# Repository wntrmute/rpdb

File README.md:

# Robot Power Distribution Board

This is a simple power distribution board that offers direct output to a motor controller, stable 5V and 3.3V rails, and an I2C expander.

## Version history

* [4.0](v4/) - added power and motor LEDs with SMD resistors
* [3.0](v3/) - updated silkscreen to improve capacitor placement
* [2.0](v2/) - first working prototype.

## Specifications

* Input voltage: 6-12V
* Max current: 1.2A draw through the 5V and 800 mA through the 3.3V rails

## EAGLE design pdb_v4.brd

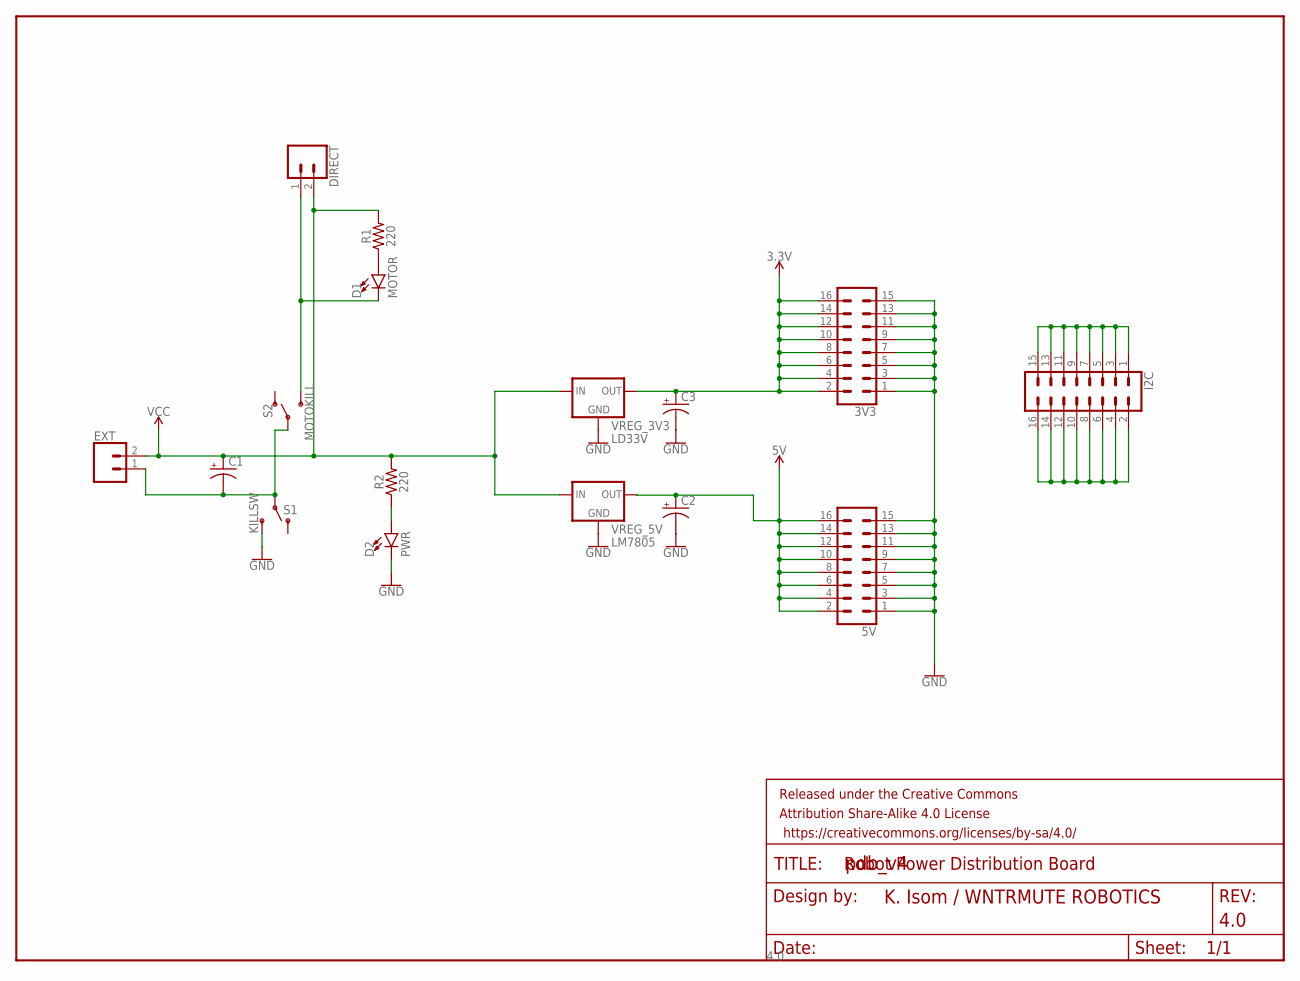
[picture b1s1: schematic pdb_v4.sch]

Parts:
3V3, 5V: CONN_08X2_HEADER; 2X8
C1: 1000uF; CPOL-RADIAL-5MM-10MM
C2, C3: 100uF; E5-8,5
D1: MOTOR; LED_3MM
D2: PWR; LED_3MM
DIRECT: CONN_025MM; SCREWTERMINAL-5MM-2
EXT: CONN_025MM; SCREWTERMINAL-5MM-2
FRAME1: FRAME-LETTERNO_PACKAGE; DUMMY
I2C: CONN_08X2_HEADER; 2X8
R1, R2: 220; 0603
S1: KILLSW; SWITCH_SPDT_PTH_11.6X4.0MM_LOCK
S2: MOTOKILL; SWITCH_SPDT_PTH_11.6X4.0MM_LOCK
VREG_3V3: LD33V; 78XXL
VREG_5V: LM7805; TO-220-ALT

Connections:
3.3V: 3V3.2, 3V3.4, 3V3.6, 3V3.8, 3V3.10, 3V3.12, 3V3.14, 3V3.16, C3.+, VREG_3V3.GND (OUT)
5V: 5V.2, 5V.4, 5V.6, 5V.8, 5V.10, 5V.12, 5V.14, 5V.16, C2.+, VREG_5V.OUT
GND: 3V3.1, 3V3.3, 3V3.5, 3V3.7, 3V3.9, 3V3.11, 3V3.13, 3V3.15, 5V.1, 5V.3, 5V.5, 5V.7, 5V.9, 5V.11, 5V.13, 5V.15, C2.-, C3.-, D2.K (C), S1.3 (S), VREG_3V3.IN (GND), VREG_5V.GND
unnamed: C1.-, EXT.1, S1.2, S2.2
unnamed: D1.A, R1.1
unnamed: D2.A, R2.1
unnamed: I2C.1, I2C.3, I2C.5, I2C.7, I2C.9, I2C.11, I2C.13, I2C.15
unnamed: I2C.2, I2C.4, I2C.6, I2C.8, I2C.10, I2C.12, I2C.14, I2C.16
unnamed: D1.K (C), DIRECT.1, S2.3 (S)
VCC: C1.+, DIRECT.2, EXT.2, R1.2, R2.2, VREG_3V3.OUT (IN), VREG_5V.IN

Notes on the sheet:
Robot Power Distribution Board

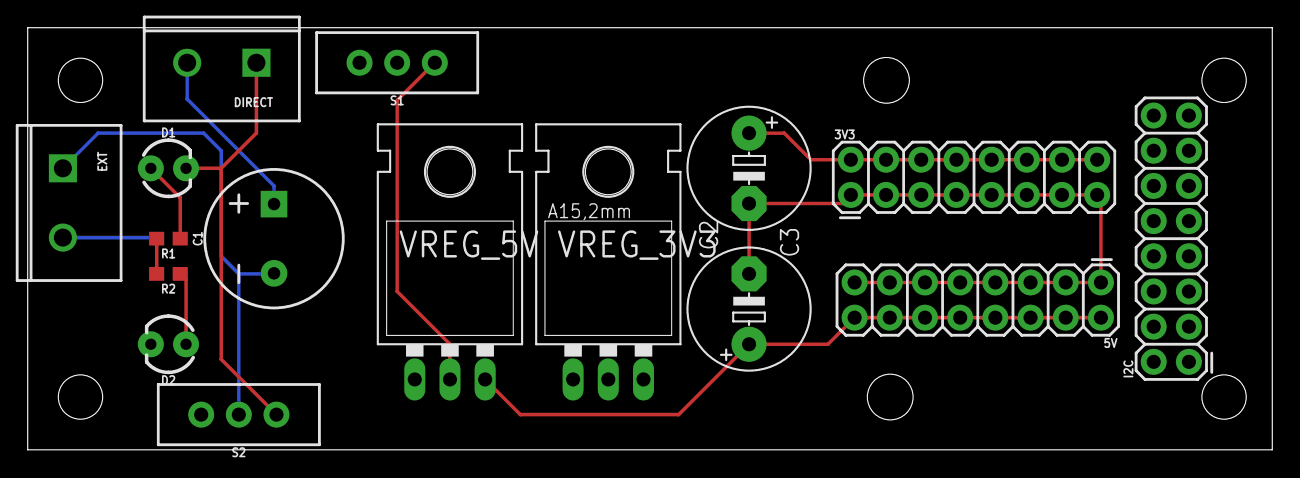
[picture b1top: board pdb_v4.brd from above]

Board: 2 copper layers, 89.8 x 30.5 mm, 17 parts (0 on the bottom side), 10 nets.

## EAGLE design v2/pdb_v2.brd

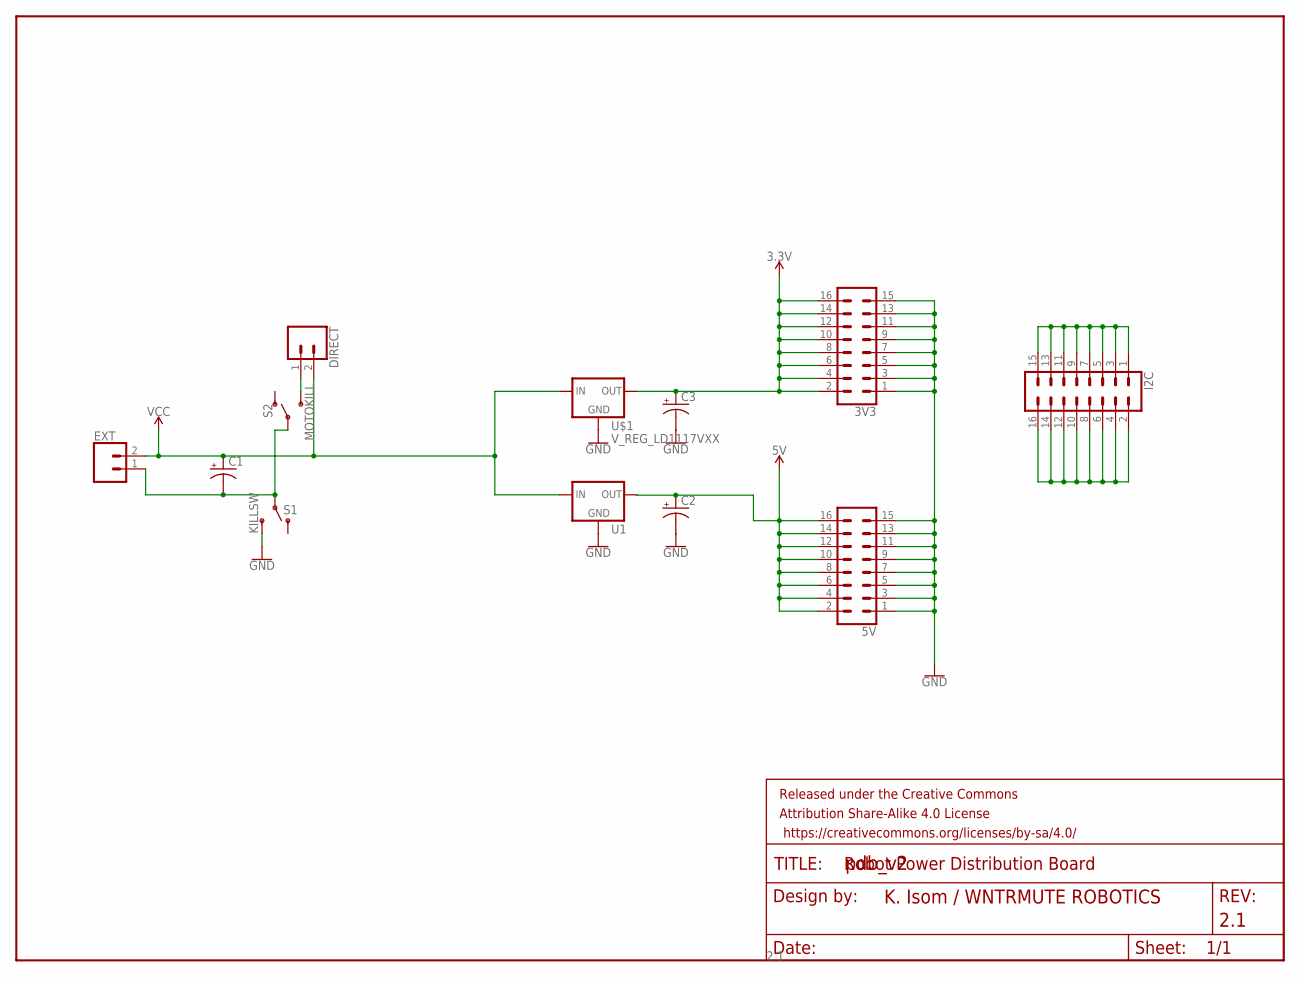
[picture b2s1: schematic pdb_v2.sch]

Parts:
3V3, 5V: CONN_08X2_HEADER; 2X8
C1: 1000µF; E5-10,5
C2, C3: 100uF; E5-8,5
DIRECT: CONN_025MM; SCREWTERMINAL-5MM-2
EXT: CONN_025MM; SCREWTERMINAL-5MM-2
FRAME1: FRAME-LETTERNO_PACKAGE; DUMMY
I2C: CONN_08X2_HEADER; 2X8
S1: KILLSW; SWITCH_SPDT_PTH_11.6X4.0MM_LOCK
S2: MOTOKILL; SWITCH_SPDT_PTH_11.6X4.0MM_LOCK
U1: V_REG_78XX-TO-220; TO-220-ALT
U$1: V_REG_LD1117VXX; 78XXL

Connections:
3.3V: 3V3.2, 3V3.4, 3V3.6, 3V3.8, 3V3.10, 3V3.12, 3V3.14, 3V3.16, C3.+, U$1.GND (OUT)
5V: 5V.2, 5V.4, 5V.6, 5V.8, 5V.10, 5V.12, 5V.14, 5V.16, C2.+, U1.OUT
GND: 3V3.1, 3V3.3, 3V3.5, 3V3.7, 3V3.9, 3V3.11, 3V3.13, 3V3.15, 5V.1, 5V.3, 5V.5, 5V.7, 5V.9, 5V.11, 5V.13, 5V.15, C2.-, C3.-, S1.3 (S), U1.GND, U$1.IN (GND)
unnamed: C1.-, EXT.1, S1.2, S2.2
unnamed: I2C.1, I2C.3, I2C.5, I2C.7, I2C.9, I2C.11, I2C.13, I2C.15
unnamed: I2C.2, I2C.4, I2C.6, I2C.8, I2C.10, I2C.12, I2C.14, I2C.16
unnamed: DIRECT.1, S2.3 (S)
VCC: C1.+, DIRECT.2, EXT.2, U1.IN, U$1.OUT (IN)

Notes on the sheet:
Robot Power Distribution Board

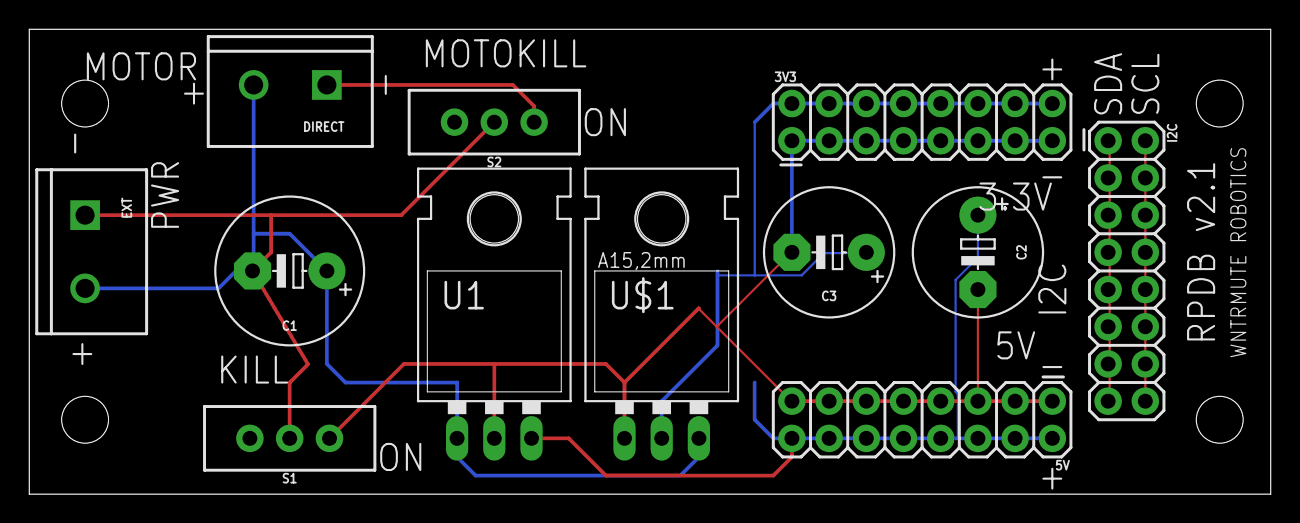
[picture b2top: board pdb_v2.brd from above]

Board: 2 copper layers, 84.8 x 31.7 mm, 13 parts (0 on the bottom side), 8 nets.

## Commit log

2019-07-31 Initial import of boards.
2019-07-31 Add README.
    Start documenting the board.
2019-07-31 Reorg and cleanup
2019-07-31 start v3 docs
2019-08-01 Dumping a load of stuff.
2019-08-01 Remove net.
2019-08-01 Clean up BOM CSVs.

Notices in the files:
parts and their libraries:
SparkFun-Connectors: Licensing: Creative Commons ShareAlike 4.0 International - https://creativecommons.org/licenses/by-sa/4.0
SparkFun-Aesthetics: Released under the Creative Commons Attribution Share-Alike 4.0 License
SparkFun-Aesthetics: https://creativecommons.org/licenses/by-sa/4.0
